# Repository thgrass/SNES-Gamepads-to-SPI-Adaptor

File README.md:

# SNES-Gamepads-to-SPI-Adaptor
A PCB that converts two SNES controllers to full SPI devices (KiCad 8+ project).

# Description
SNES controllers are already almost SPI type-1 devices if you use the CS pin as the controller's latch pin. This will already work on an SPI bus with one controller and no other devices present. To make other devices work on the same bus (a second controller as a notable example), you have to make the controller shut up when it is not used. The IC on this Adaptor board does exactly this for two SNES controllers.
The controllers share the SPI port's data, clock and power pins, but each controller requires its own chip select (CS) pin. For example, you can connect this adaptor directly with a Raspberry Pi, as its GPIO header exposes a SPI port with two CS pins.

# Why?
To fulfill retro gaming needs on various hardware, old and new. 

# Credits
Information about the SNES controller protocol and the IC being used are sourced from here:
https://circuitcellar.com/research-design-hub/projects/interfacing-with-video-game-controllers/
https://www.youtube.com/watch?v=NGiFlDPaB0o

KiCad-Libraries for the SNES controller port have been taken from here:
https://github.com/pdaehne/SNES-Userport-Adapter

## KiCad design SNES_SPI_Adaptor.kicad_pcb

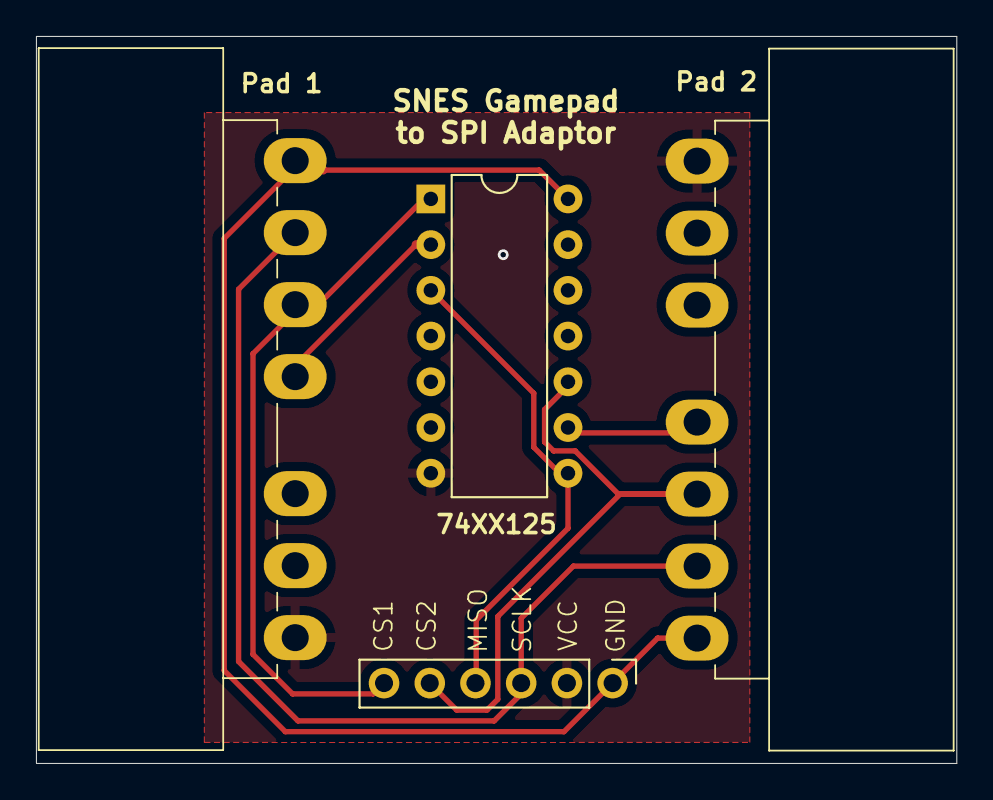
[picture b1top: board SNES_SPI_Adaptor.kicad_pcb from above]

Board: 2 copper layers, 51.1 x 40.4 mm, 4 parts (0 on the bottom side), 8 nets.

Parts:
74XX125: 74AHCT125; DIP-14_W7.62mm
J1, J3: SNES Controller Socket; SNES_Controller_Socket
J2: SPI_generic; PinHeader_1x06_P2.54mm_Vertical

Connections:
+5V: 74XX125.14 (VCC), J1.1 (VCC), J2.6, J3.1 (VCC)
/CS1: 74XX125.1, J1.3 (Latch), J2.1
/CS2: 74XX125.10, J2.2, J3.3 (Latch)
/Clock: J1.2 (Clock), J2.4, J3.2 (Clock)
/Data_1: 74XX125.2, J1.4 (Data)
/Data_2: 74XX125.9, J3.4 (Data)
/MISO: 74XX125.3, 74XX125.8, J2.3
GND: 74XX125.7 (GND), J1.7 (GND), J2.5, J3.7 (GND)

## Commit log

2026-05-27 Enhance README with additional details and credits
    Expanded the README with detailed description and credits.
2026-05-27 Enhance README with image and detailed description
    Added a 3D preview image and expanded the description of the SNES to SPI adaptor functionality.
